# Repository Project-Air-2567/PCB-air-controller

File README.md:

# PCB-air-controller
# relay hrs4h s dc5v: https://www.es.co.th/Schemetic/PDF/HRS4.PDF
# temperature-sensor: full-waterproof-temperature-sensor

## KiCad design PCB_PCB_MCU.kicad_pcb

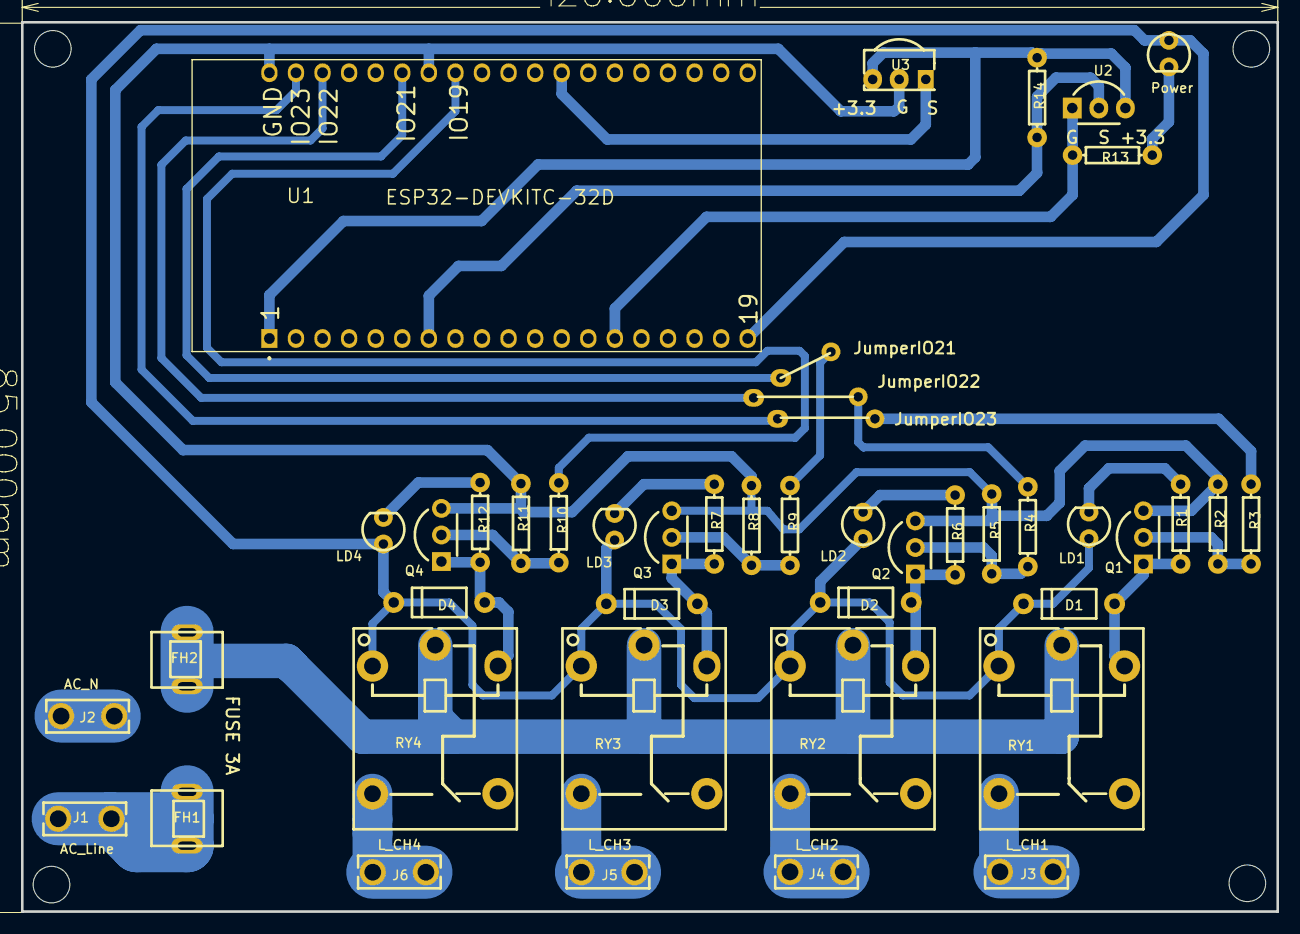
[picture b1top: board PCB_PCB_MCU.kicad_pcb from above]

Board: 2 copper layers, 120.0 x 85.0 mm, 52 parts (0 on the bottom side), 28 nets.

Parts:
D1, D2, D3, D4: 1N4007; DO-41_BD2.4-L4.7-P8.70-D0.9-RD
FH1, FH2: 5x20 RHOS Fuse clip/seat; FUSE-TH_5X20RHOSFUSECLIP-SEAT
Hole_gge5052: Hole_gge5052
Hole_gge5070: Hole_gge5070
Hole_gge5085: Hole_gge5085
Hole_gge5100: Hole_gge5100
J1: AC_Line; CONN-TH_63849-1
J2: AC_N; CONN-TH_63849-1
J3: L_CH1; CONN-TH_63849-1
J4: L_CH2; CONN-TH_63849-1
J5: L_CH3; CONN-TH_63849-1
J6: L_CH4; CONN-TH_63849-1
LD1: CH1; LED-TH_BD3.0_RED
LD2: CH2; LED-TH_BD3.0_RED
LD3: CH3; LED-TH_BD3.0_RED
LD4: CH4; LED-TH_BD3.0_RED
LED5: Power; LED-TH_BD3.0_RED
Pad_gge10031: Pad_gge10031
Pad_gge10055: Pad_gge10055
Pad_gge10125: Pad_gge10125
Pad_gge10216: Pad_gge10216
Pad_gge10248: Pad_gge10248
Pad_gge10293: Pad_gge10293
Q1, Q2, Q3, Q4: BC338; TO-92-3_L4.9-W3.7-P2.54-L
R1, R6, R7, R12: 1.5k; R_AXIAL-0.3
R2, R5, R8, R11: 10k; R_AXIAL-0.3
R3, R4, R9, R10: 1k; R_AXIAL-0.3
R13: 470; R_AXIAL-0.3
R14: 3K; R_AXIAL-0.3
RY1: CH1; RELAY-TH_SRD-XXVDC-XL-C
RY2: CH2; RELAY-TH_SRD-XXVDC-XL-C
RY3: CH3; RELAY-TH_SRD-XXVDC-XL-C
RY4: CH4; RELAY-TH_SRD-XXVDC-XL-C
U1: ESP32-DEVKITC-32D; COMM-SMD_ESP32-DEVKITC-32D
U2: DS18B20+T&R; TO-92-3_L4.9-W3.7-P2.54-L
U3: VS1838B; OPTO-TH_VS1838B

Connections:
+3.3V: R14.1, U1.J2-1, U2.3, U3.3
+5V: D1.1, D2.1, D3.1, D4.1, LD1.1, LD2.1, LD3.1, LD4.1, LED5.1, RY1.1, RY2.1, RY3.1, RY4.1, U1.J2-19
D2_2: D2.2, Q2.1, R6.1, RY2.4
D4_2: D4.2, Q4.1, R12.1, RY4.4
FH1_1: FH1.1, J1.1
GND: Q1.3, Q2.3, Q3.3, Q4.3, R2.1, R5.1, R8.1, R11.1, R13.1, U1.J2-14, U1.J3-1, U1.J3-7, U2.1, U3.2
LD1_2: LD1.2, R1.2
LD3_2: LD3.2, R7.2
LED5_2: LED5.2, R13.2
Q1_1: D1.2, Q1.1, R1.1, RY1.4
Q1_2: Q1.2, R2.2, R3.1
Q3_1: D3.2, Q3.1, R7.1, RY3.4
Q3_2: Q3.2, R8.2, R9.1
R4_1: Q2.2, R4.1, R5.2
R6_2: LD2.2, R6.2
R10_1: Q4.2, R10.1, R11.2
R12_2: LD4.2, R12.2
RY1_2: J3.1, RY1.2
RY1_5: FH2.1, RY1.5, RY2.5, RY3.5, RY4.5
RY2_2: J4.1, RY2.2
RY3_2: J5.1, RY3.2
RY4_2: J6.1, RY4.2
U1_J2-7: R14.2, U1.J2-7, U2.2
U1_J3-2: Pad_gge10031.1, Pad_gge10055.2, R3.2, U1.J3-2
U1_J3-3: Pad_gge10125.2, Pad_gge10216.1, R4.2, U1.J3-3
U1_J3-6: Pad_gge10248.2, Pad_gge10293.2, R9.2, U1.J3-6
U1_J3-8: R10.2, U1.J3-8
U1_J3-12: U1.J3-12, U3.1
